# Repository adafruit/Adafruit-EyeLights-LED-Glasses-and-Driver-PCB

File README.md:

## Adafruit EyeLights LED Glasses and Driver PCB

<a href="http://www.adafruit.com/products/5217"><br/>
Click here to purchase the EyeLights Glasses Driver from the Adafruit shop</a>
<a href="http://www.adafruit.com/products/5210"><br/>
Click here to purchase the EyeLights Glasses from the Adafruit shop</a>

PCB files for the Adafruit EyeLights LED Glasses and Driver. 

Format is EagleCAD schematic and board layout
* https://www.adafruit.com/product/5217
* https://www.adafruit.com/product/5210

### Description

This board is designed to be a thin, bluetooth-enabled driver board for our Adafruit LED Glasses RGB LED matrix. That said, it's a perfectly good stand-alone development board for the Nordic nRF52840 chipset, with a very slim design, optional LiPo battery support, a few sensors, and a Stemma QT port for adding other devices or sensors with I2C plug-and-play.

The driver looks a little like a Feather but it does not have any breakout pins to keep it very compact. If you need access to GPIO pins, we recommend an nRF52840 ItsyBitsy, nRF52840 Feather or Feather Sense.

In exchange for GPIO outputs, we added some sensors on instead: each board comes with a LIS3DH triple-axis accelerometer that can be used for motion and orientation sensing, and a PDM digital microphone for audio sensing. To add more sensors or connect to the LED Glasses front panel, there's a  STEMMA QT connector for plug-and-play I2C support.

Unlike our Itsy/Feather boards, this driver also comes with a proper on/off switch which will cut power to the microcontroller and external sensors. There's optional LiPo charge support because we think that many folks will want to power this board with AAA or coin cell batteries. If you'd like to enable LiPo charging, short the jumper on the back and then make sure to only use 4.2V/3.7V rechargeable batteries in the battery port.

The nRF52840 is a lovely Bluetooth LE microcontroller, with good support in both Arduino and CircuitPython. It feathers a Cortex M4 processor with 1 MB of FLASH and 256KB of SRAM. Best of all, it's got that native USB! Finally, no need for a separate USB serial chip like CP2104 or FT232. Serial is handled as a USB CDC descriptor, and the chip can act like a keyboard, mouse, MIDI device or even disk drive. This chip has TinyUSB support - that means you can use it with Arduino as a native USB device and act as UART (CDC), HID, Mass Storage, MIDI and more!

Board Features:

* ARM Cortex M4F (with HW floating point acceleration) running at 64MHz
* 1MB flash and 256KB SRAM
* Bluetooth Low Energy compatible 2.4GHz radio (Details available in the nRF52840 product specification)
* FCC / IC / TELEC certified module with up to +8dBm output power
* 2MB external QSPI flash for CircuitPython file storage
* Built in LIS3DH accelerometer and PDM microphone
* Red LED for general purpose blinking, plus a tiny NeoPixel for colorful feedback
* STEMMA QT connector for plug-and-play I2C support.
* JST PH 2-pin battery port with optional LiPoly charger
* 4 mounting holes/slots
* Reset button and User button
* Native USB supported by every OS - can be used in Arduino or CircuitPython as USB serial console, Keyboard/Mouse HID, even a little disk drive for storing Python scripts.
* Can be used with Arduino IDE or CircuitPython
* Comes pre-loaded with the UF2 bootloader, which looks like a USB storage key. Simply drag firmware on to program, no special tools or drivers needed! It can be used to load up CircuitPython or Arduino IDE

For developers, we pre-programed the chip with our UF2 bootloader, which can use either command line UART programming with nrfutil (we use this for Arduino) or drag-n-drop mass storage, for CircuitPython installation and also because mass-storage-drive bootloaders make updating firmware so easy. Want to program the chip directly? You can use our command line tools with your favorite editor and toolchain. If you want to use an SWD programmer/debugger (for even more advanced usage), we have broken out the SWD pads for easy soldering.

Have you always wanted to upgrade your ensemble with a creepy-cool creature PCB silkscreen and an eye-blistering arrangement of LEDs? We love to put NeoPixels on our face, as evidenced by our many glowy LED glasses projects. Each of these requires quite a bit of soldering, and the cost of each NeoPixel adds up quickly. So we wanted to make a PCB assembly that can be used by any microcontroller to make glamorous face-tronics.

The Adafruit LED Glasses Front Panel has 116 artfully arranged 2x2mm RGB LEDs, all controlled with an IS31FL3741 I2C Driver that handles all the PWMing, so it's plug-and-play with almost any microcontroller.

On each side are STEMMA QT / JST-SH plugs - use these with one of our cables to attach it to your driver board of choice. Of course, you can pick left or right, then if you want to add on more hardware, like an accelerometer or light sensor, you can chain onto the other side. There's also six mounting holes for attaching to a glasses frame of your choosing - we recommend getting some 'fashion frames' from the mall or a street vendor, they're all the style and will provide a great mechanical support.

We have four different silkscreen designs: Bug, Wolf, Cat, and Dragon (peep those fearsome fangs!) Each design is exactly the same mechanically and electrically, the only difference is what is silkscreened on top of the PCB.

Gaze upon these features:

* IS31Fl3741 LED driver chip uses I2C to control the LEDs with 8-bit PWM per color (24-bit per RGB LED), write pixel data and it will handle the matrix driving automatically.
* Power and communicate over STEMMA QT for easy wiring
* The LEDs are arranged as 2 x 24-LED rings around each eye and an overlapping 16x5 matrix. The matrix has two bottom pixels 'missing' over the nose. Some LEDs are shared between both matrix and rings!
* Arduino and CircuitPython/Python library support

### License

Adafruit invests time and resources providing this open source design, please support Adafruit and open-source hardware by purchasing products from [Adafruit](https://www.adafruit.com)!

Designed by Limor Fried/Ladyada for Adafruit Industries.

Creative Commons Attribution/Share-Alike, all text above must be included in any redistribution. 
See license.txt for additional details.

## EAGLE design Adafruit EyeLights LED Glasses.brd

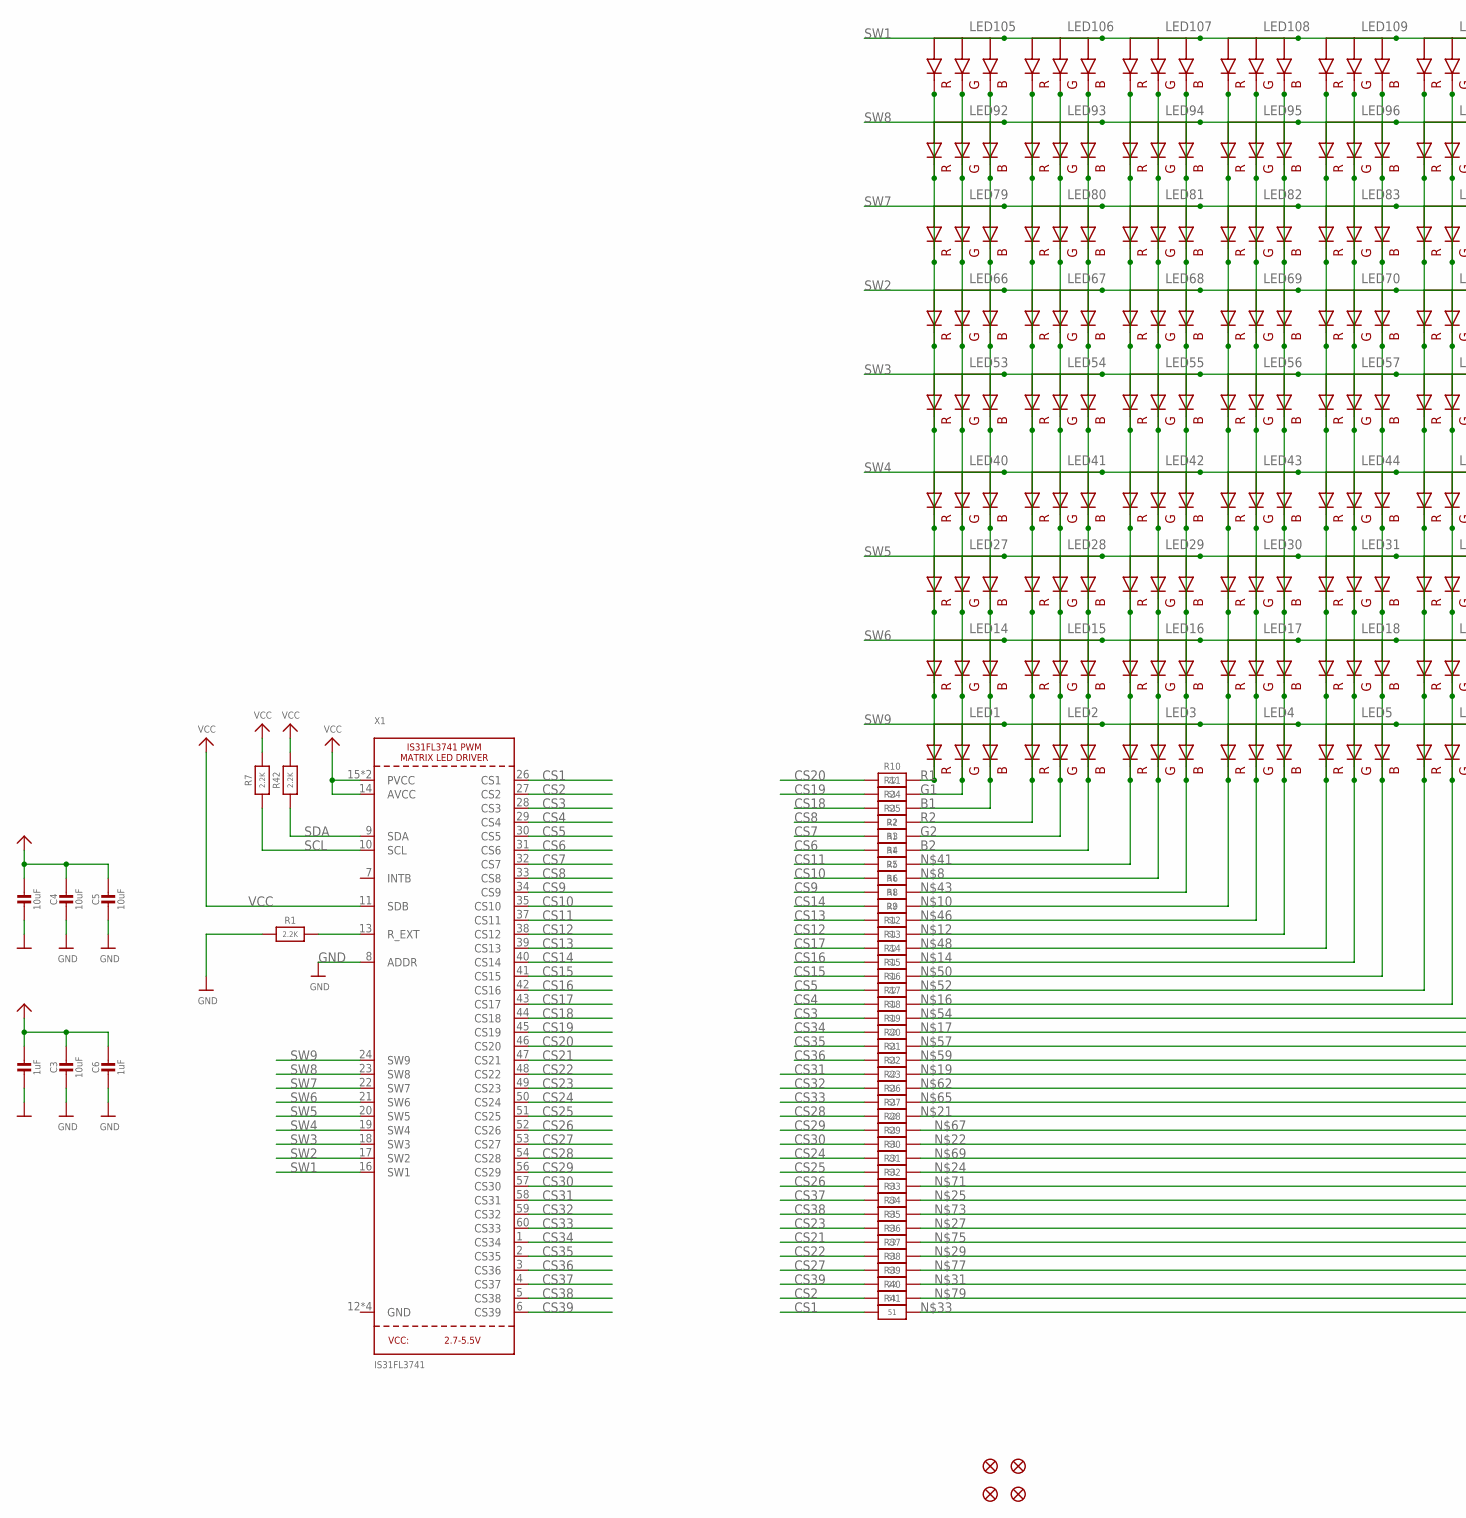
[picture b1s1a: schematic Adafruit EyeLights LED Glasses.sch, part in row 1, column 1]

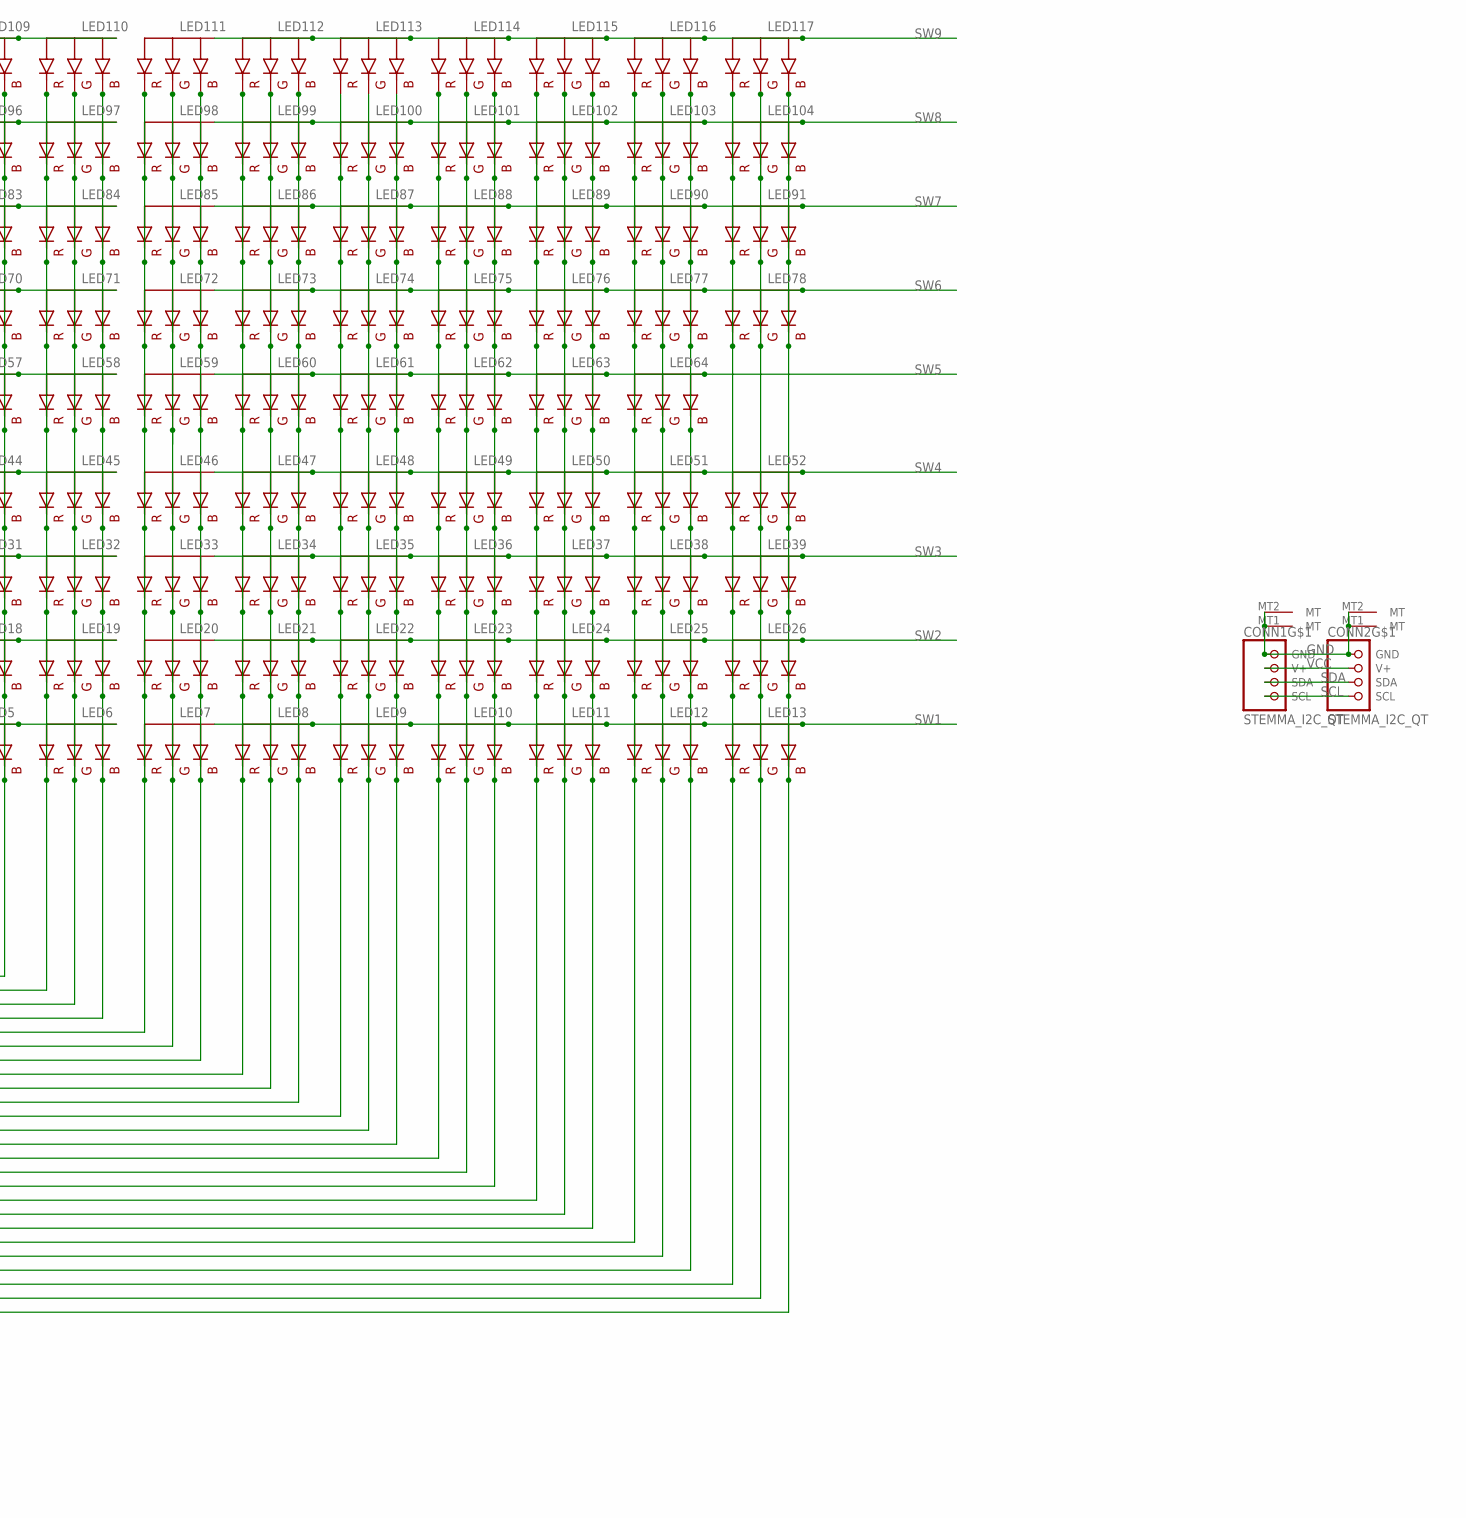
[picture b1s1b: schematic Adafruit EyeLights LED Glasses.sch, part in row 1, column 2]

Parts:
C1, C3, C4, C5: 10uF; 0805-NO
C2, C6: 1uF; 0603-NO
CONN1, CONN2: STEMMA_I2C_QT; JST_SH4
FID1, FID2, FID3, FID4: FIDUCIAL_1MM
LED1, LED2, LED3, LED4, LED5, LED6, LED7, LED8, LED9, LED10, LED11, LED12, LED13, LED14, LED15, LED16, LED17, LED18, LED19, LED20, LED21, LED22, LED23, LED24, LED25, LED26, LED27, LED28, LED29, LED30, LED31, LED32, LED33, LED34, LED35, LED36, LED37, LED38, LED39, LED40, LED41, LED42, LED43, LED44, LED45, LED46, LED47, LED48, LED49, LED50, LED51, LED52, LED53, LED54, LED55, LED56, LED57, LED58, LED59, LED60, LED61, LED62, LED63, LED64, LED66, LED67, LED68, LED69, LED70, LED71, LED72, LED73, LED74, LED75, LED76, LED77, LED78, LED79, LED80, LED81, LED82, LED83, LED84, LED85, LED86, LED87, LED88, LED89, LED90, LED91, LED92, LED93, LED94, LED95, LED96, LED97, LED98, LED99, LED100, LED101, LED102, LED103, LED104, LED105, LED106, LED107, LED108, LED109, LED110, LED111, LED112, LED113, LED114, LED115, LED116, LED117: RGBLED_CA_2121; RGBLED_2121
R1, R7, R42: 2.2K; 0603-NO
R2, R3, R5, R6, R9, R11, R12, R14, R15, R17, R18, R20, R21, R23, R24, R26, R28, R29, R31, R32, R34, R35, R37, R38, R40, R41: 51; 0603-NO
R4, R8, R10, R13, R16, R19, R22, R25, R27, R30, R33, R36, R39: 22; 0603-NO
X1: IS31FL3741; QFN60_7MM

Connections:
B1: LED1.B (BLUE), LED14.B (BLUE), LED27.B (BLUE), LED40.B (BLUE), LED53.B (BLUE), LED66.B (BLUE), LED79.B (BLUE), LED92.B (BLUE), LED105.B (BLUE), R24.2
B2: LED2.B (BLUE), LED15.B (BLUE), LED28.B (BLUE), LED41.B (BLUE), LED54.B (BLUE), LED67.B (BLUE), LED80.B (BLUE), LED93.B (BLUE), LED106.B (BLUE), R3.2
CS1: R41.1, X1.26 (CS1)
CS2: R40.1, X1.27 (CS2)
CS3: R18.1, X1.28 (CS3)
CS4: R17.1, X1.29 (CS4)
CS5: R16.1, X1.30 (CS5)
CS6: R3.1, X1.31 (CS6)
CS7: R2.1, X1.32 (CS7)
CS8: R25.1, X1.33 (CS8)
CS9: R6.1, X1.34 (CS9)
CS10: R5.1, X1.35 (CS10)
CS11: R4.1, X1.37 (CS11)
CS12: R12.1, X1.38 (CS12)
CS13: R9.1, X1.39 (CS13)
CS14: R8.1, X1.40 (CS14)
CS15: R15.1, X1.41 (CS15)
CS16: R14.1, X1.42 (CS16)
CS17: R13.1, X1.43 (CS17)
CS18: R24.1, X1.44 (CS18)
CS19: R11.1, X1.45 (CS19)
CS20: R10.1, X1.46 (CS20)
CS21: R36.1, X1.47 (CS21)
CS22: R37.1, X1.48 (CS22)
CS23: R35.1, X1.49 (CS23)
CS24: R30.1, X1.50 (CS24)
CS25: R31.1, X1.51 (CS25)
CS26: R32.1, X1.52 (CS26)
CS27: R38.1, X1.53 (CS27)
CS28: R27.1, X1.54 (CS28)
CS29: R28.1, X1.56 (CS29)
CS30: R29.1, X1.57 (CS30)
CS31: R22.1, X1.58 (CS31)
CS32: R23.1, X1.59 (CS32)
CS33: R26.1, X1.60 (CS33)
CS34: R19.1, X1.1 (CS34)
CS35: R20.1, X1.2 (CS35)
CS36: R21.1, X1.3 (CS36)
CS37: R33.1, X1.4 (CS37)
CS38: R34.1, X1.5 (CS38)
CS39: R39.1, X1.6 (CS39)
G1: LED1.G (GREEN), LED14.G (GREEN), LED27.G (GREEN), LED40.G (GREEN), LED53.G (GREEN), LED66.G (GREEN), LED79.G (GREEN), LED92.G (GREEN), LED105.G (GREEN), R11.2
G2: LED2.G (GREEN), LED15.G (GREEN), LED28.G (GREEN), LED41.G (GREEN), LED54.G (GREEN), LED67.G (GREEN), LED80.G (GREEN), LED93.G (GREEN), LED106.G (GREEN), R2.2
GND: C1.2, C2.2, C3.2, C4.2, C5.2, C6.2, CONN1.1 (GND), CONN1.MT1 (MT), CONN1.MT2 (MT), CONN2.1 (GND), CONN2.MT1 (MT), CONN2.MT2 (MT), R1.1, X1.8 (ADDR), X1.12 (GND), X1.36 (GND), X1.55 (GND), X1.THERMAL (GND)
unnamed: R1.2, X1.13 (R_EXT)
unnamed: LED3.G (GREEN), LED16.G (GREEN), LED29.G (GREEN), LED42.G (GREEN), LED55.G (GREEN), LED68.G (GREEN), LED81.G (GREEN), LED94.G (GREEN), LED107.G (GREEN), R5.2
unnamed: LED4.R (RED), LED17.R (RED), LED30.R (RED), LED43.R (RED), LED56.R (RED), LED69.R (RED), LED82.R (RED), LED95.R (RED), LED108.R (RED), R8.2
unnamed: LED4.B (BLUE), LED17.B (BLUE), LED30.B (BLUE), LED43.B (BLUE), LED56.B (BLUE), LED69.B (BLUE), LED82.B (BLUE), LED95.B (BLUE), LED108.B (BLUE), R12.2
unnamed: LED5.G (GREEN), LED18.G (GREEN), LED31.G (GREEN), LED44.G (GREEN), LED57.G (GREEN), LED70.G (GREEN), LED83.G (GREEN), LED96.G (GREEN), LED109.G (GREEN), R14.2
unnamed: LED6.G (GREEN), LED19.G (GREEN), LED32.G (GREEN), LED45.G (GREEN), LED58.G (GREEN), LED71.G (GREEN), LED84.G (GREEN), LED97.G (GREEN), LED110.G (GREEN), R17.2
unnamed: LED7.R (RED), LED20.R (RED), LED33.R (RED), LED46.R (RED), LED59.R (RED), LED72.R (RED), LED85.R (RED), LED98.R (RED), LED111.R (RED), R19.2
unnamed: LED8.R (RED), LED21.R (RED), LED34.R (RED), LED47.R (RED), LED60.R (RED), LED73.R (RED), LED86.R (RED), LED99.R (RED), LED112.R (RED), R22.2
unnamed: LED9.R (RED), LED22.R (RED), LED35.R (RED), LED48.R (RED), LED61.R (RED), LED74.R (RED), LED87.R (RED), LED100.R (RED), LED113.R (RED), R27.2
unnamed: LED9.B (BLUE), LED22.B (BLUE), LED35.B (BLUE), LED48.B (BLUE), LED61.B (BLUE), LED74.B (BLUE), LED87.B (BLUE), LED100.B (BLUE), LED113.B (BLUE), R29.2
unnamed: LED10.G (GREEN), LED23.G (GREEN), LED36.G (GREEN), LED49.G (GREEN), LED62.G (GREEN), LED75.G (GREEN), LED88.G (GREEN), LED101.G (GREEN), LED114.G (GREEN), R31.2
unnamed: LED11.R (RED), LED24.R (RED), LED37.R (RED), LED50.R (RED), LED63.R (RED), LED76.R (RED), LED89.R (RED), LED102.R (RED), LED115.R (RED), R33.2
unnamed: LED11.B (BLUE), LED24.B (BLUE), LED37.B (BLUE), LED50.B (BLUE), LED63.B (BLUE), LED76.B (BLUE), LED89.B (BLUE), LED102.B (BLUE), LED115.B (BLUE), R35.2
unnamed: LED12.G (GREEN), LED25.G (GREEN), LED38.G (GREEN), LED51.G (GREEN), LED64.G (GREEN), LED77.G (GREEN), LED90.G (GREEN), LED103.G (GREEN), LED116.G (GREEN), R37.2
unnamed: LED13.R (RED), LED26.R (RED), LED39.R (RED), LED52.R (RED), LED78.R (RED), LED91.R (RED), LED104.R (RED), LED117.R (RED), R39.2
unnamed: LED13.B (BLUE), LED26.B (BLUE), LED39.B (BLUE), LED52.B (BLUE), LED78.B (BLUE), LED91.B (BLUE), LED104.B (BLUE), LED117.B (BLUE), R41.2
unnamed: LED3.R (RED), LED16.R (RED), LED29.R (RED), LED42.R (RED), LED55.R (RED), LED68.R (RED), LED81.R (RED), LED94.R (RED), LED107.R (RED), R4.2
unnamed: LED3.B (BLUE), LED16.B (BLUE), LED29.B (BLUE), LED42.B (BLUE), LED55.B (BLUE), LED68.B (BLUE), LED81.B (BLUE), LED94.B (BLUE), LED107.B (BLUE), R6.2
unnamed: LED4.G (GREEN), LED17.G (GREEN), LED30.G (GREEN), LED43.G (GREEN), LED56.G (GREEN), LED69.G (GREEN), LED82.G (GREEN), LED95.G (GREEN), LED108.G (GREEN), R9.2
unnamed: LED5.R (RED), LED18.R (RED), LED31.R (RED), LED44.R (RED), LED57.R (RED), LED70.R (RED), LED83.R (RED), LED96.R (RED), LED109.R (RED), R13.2
unnamed: LED5.B (BLUE), LED18.B (BLUE), LED31.B (BLUE), LED44.B (BLUE), LED57.B (BLUE), LED70.B (BLUE), LED83.B (BLUE), LED96.B (BLUE), LED109.B (BLUE), R15.2
unnamed: LED6.R (RED), LED19.R (RED), LED32.R (RED), LED45.R (RED), LED58.R (RED), LED71.R (RED), LED84.R (RED), LED97.R (RED), LED110.R (RED), R16.2
unnamed: LED6.B (BLUE), LED19.B (BLUE), LED32.B (BLUE), LED45.B (BLUE), LED58.B (BLUE), LED71.B (BLUE), LED84.B (BLUE), LED97.B (BLUE), LED110.B (BLUE), R18.2
unnamed: LED7.G (GREEN), LED20.G (GREEN), LED33.G (GREEN), LED46.G (GREEN), LED59.G (GREEN), LED72.G (GREEN), LED85.G (GREEN), LED98.G (GREEN), LED111.G (GREEN), R20.2
unnamed: LED7.B (BLUE), LED20.B (BLUE), LED33.B (BLUE), LED46.B (BLUE), LED59.B (BLUE), LED72.B (BLUE), LED85.B (BLUE), LED98.B (BLUE), LED111.B (BLUE), R21.2
unnamed: LED8.G (GREEN), LED21.G (GREEN), LED34.G (GREEN), LED47.G (GREEN), LED60.G (GREEN), LED73.G (GREEN), LED86.G (GREEN), LED99.G (GREEN), LED112.G (GREEN), R23.2
unnamed: LED8.B (BLUE), LED21.B (BLUE), LED34.B (BLUE), LED47.B (BLUE), LED60.B (BLUE), LED73.B (BLUE), LED86.B (BLUE), LED99.B (BLUE), LED112.B (BLUE), R26.2
unnamed: LED9.G (GREEN), LED22.G (GREEN), LED35.G (GREEN), LED48.G (GREEN), LED61.G (GREEN), LED74.G (GREEN), LED87.G (GREEN), LED100.G (GREEN), LED113.G (GREEN), R28.2
unnamed: LED10.R (RED), LED23.R (RED), LED36.R (RED), LED49.R (RED), LED62.R (RED), LED75.R (RED), LED88.R (RED), LED101.R (RED), LED114.R (RED), R30.2
unnamed: LED10.B (BLUE), LED23.B (BLUE), LED36.B (BLUE), LED49.B (BLUE), LED62.B (BLUE), LED75.B (BLUE), LED88.B (BLUE), LED101.B (BLUE), LED114.B (BLUE), R32.2
unnamed: LED11.G (GREEN), LED24.G (GREEN), LED37.G (GREEN), LED50.G (GREEN), LED63.G (GREEN), LED76.G (GREEN), LED89.G (GREEN), LED102.G (GREEN), LED115.G (GREEN), R34.2
unnamed: LED12.R (RED), LED25.R (RED), LED38.R (RED), LED51.R (RED), LED64.R (RED), LED77.R (RED), LED90.R (RED), LED103.R (RED), LED116.R (RED), R36.2
unnamed: LED12.B (BLUE), LED25.B (BLUE), LED38.B (BLUE), LED51.B (BLUE), LED64.B (BLUE), LED77.B (BLUE), LED90.B (BLUE), LED103.B (BLUE), LED116.B (BLUE), R38.2
unnamed: LED13.G (GREEN), LED26.G (GREEN), LED39.G (GREEN), LED52.G (GREEN), LED78.G (GREEN), LED91.G (GREEN), LED104.G (GREEN), LED117.G (GREEN), R40.2
R1: LED1.R (RED), LED14.R (RED), LED27.R (RED), LED40.R (RED), LED53.R (RED), LED66.R (RED), LED79.R (RED), LED92.R (RED), LED105.R (RED), R10.2
R2: LED2.R (RED), LED15.R (RED), LED28.R (RED), LED41.R (RED), LED54.R (RED), LED67.R (RED), LED80.R (RED), LED93.R (RED), LED106.R (RED), R25.2
SCL: CONN1.4 (SCL), CONN2.4 (SCL), R7.1, X1.10 (SCL)
SDA: CONN1.3 (SDA), CONN2.3 (SDA), R42.1, X1.9 (SDA)
SW1: LED7.A (VCC), LED8.A (VCC), LED9.A (VCC), LED10.A (VCC), LED11.A (VCC), LED12.A (VCC), LED13.A (VCC), LED105.A (VCC), LED106.A (VCC), LED107.A (VCC), LED108.A (VCC), LED109.A (VCC), LED110.A (VCC), X1.16 (SW1)
SW2: LED20.A (VCC), LED21.A (VCC), LED22.A (VCC), LED23.A (VCC), LED24.A (VCC), LED25.A (VCC), LED26.A (VCC), LED66.A (VCC), LED67.A (VCC), LED68.A (VCC), LED69.A (VCC), LED70.A (VCC), LED71.A (VCC), X1.17 (SW2)
SW3: LED33.A (VCC), LED34.A (VCC), LED35.A (VCC), LED36.A (VCC), LED37.A (VCC), LED38.A (VCC), LED39.A (VCC), LED53.A (VCC), LED54.A (VCC), LED55.A (VCC), LED56.A (VCC), LED57.A (VCC), LED58.A (VCC), X1.18 (SW3)
SW4: LED40.A (VCC), LED41.A (VCC), LED42.A (VCC), LED43.A (VCC), LED44.A (VCC), LED45.A (VCC), LED46.A (VCC), LED47.A (VCC), LED48.A (VCC), LED49.A (VCC), LED50.A (VCC), LED51.A (VCC), LED52.A (VCC), X1.19 (SW4)
SW5: LED27.A (VCC), LED28.A (VCC), LED29.A (VCC), LED30.A (VCC), LED31.A (VCC), LED32.A (VCC), LED59.A (VCC), LED60.A (VCC), LED61.A (VCC), LED62.A (VCC), LED63.A (VCC), LED64.A (VCC), X1.20 (SW5)
SW6: LED14.A (VCC), LED15.A (VCC), LED16.A (VCC), LED17.A (VCC), LED18.A (VCC), LED19.A (VCC), LED72.A (VCC), LED73.A (VCC), LED74.A (VCC), LED75.A (VCC), LED76.A (VCC), LED77.A (VCC), LED78.A (VCC), X1.21 (SW6)
SW7: LED79.A (VCC), LED80.A (VCC), LED81.A (VCC), LED82.A (VCC), LED83.A (VCC), LED84.A (VCC), LED85.A (VCC), LED86.A (VCC), LED87.A (VCC), LED88.A (VCC), LED89.A (VCC), LED90.A (VCC), LED91.A (VCC), X1.22 (SW7)
SW8: LED92.A (VCC), LED93.A (VCC), LED94.A (VCC), LED95.A (VCC), LED96.A (VCC), LED97.A (VCC), LED98.A (VCC), LED99.A (VCC), LED100.A (VCC), LED101.A (VCC), LED102.A (VCC), LED103.A (VCC), LED104.A (VCC), X1.23 (SW8)
SW9: LED1.A (VCC), LED2.A (VCC), LED3.A (VCC), LED4.A (VCC), LED5.A (VCC), LED6.A (VCC), LED111.A (VCC), LED112.A (VCC), LED113.A (VCC), LED114.A (VCC), LED115.A (VCC), LED116.A (VCC), LED117.A (VCC), X1.24 (SW9)
VCC: C1.1, C2.1, C3.1, C4.1, C5.1, C6.1, CONN1.2 (V+), CONN2.2 (V+), R7.2, R42.2, X1.11 (SDB), X1.14 (AVCC), X1.15 (PVCC), X1.25 (PVCC)

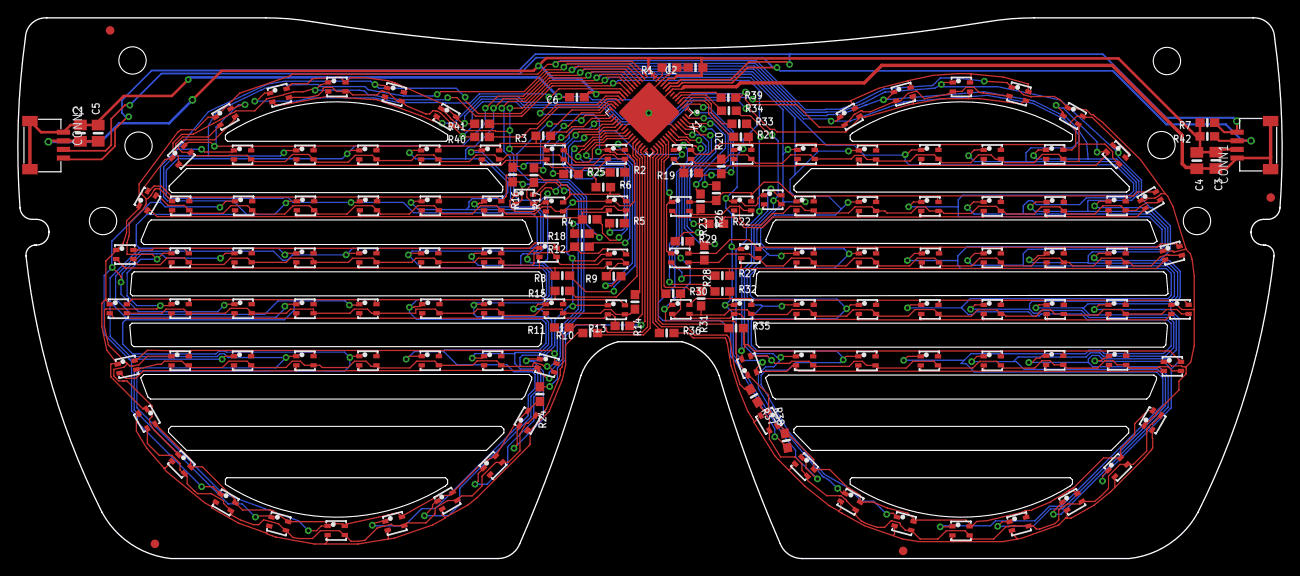
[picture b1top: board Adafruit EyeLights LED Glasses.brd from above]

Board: 2 copper layers, 147.0 x 62.9 mm, 171 parts (0 on the bottom side), 92 nets.

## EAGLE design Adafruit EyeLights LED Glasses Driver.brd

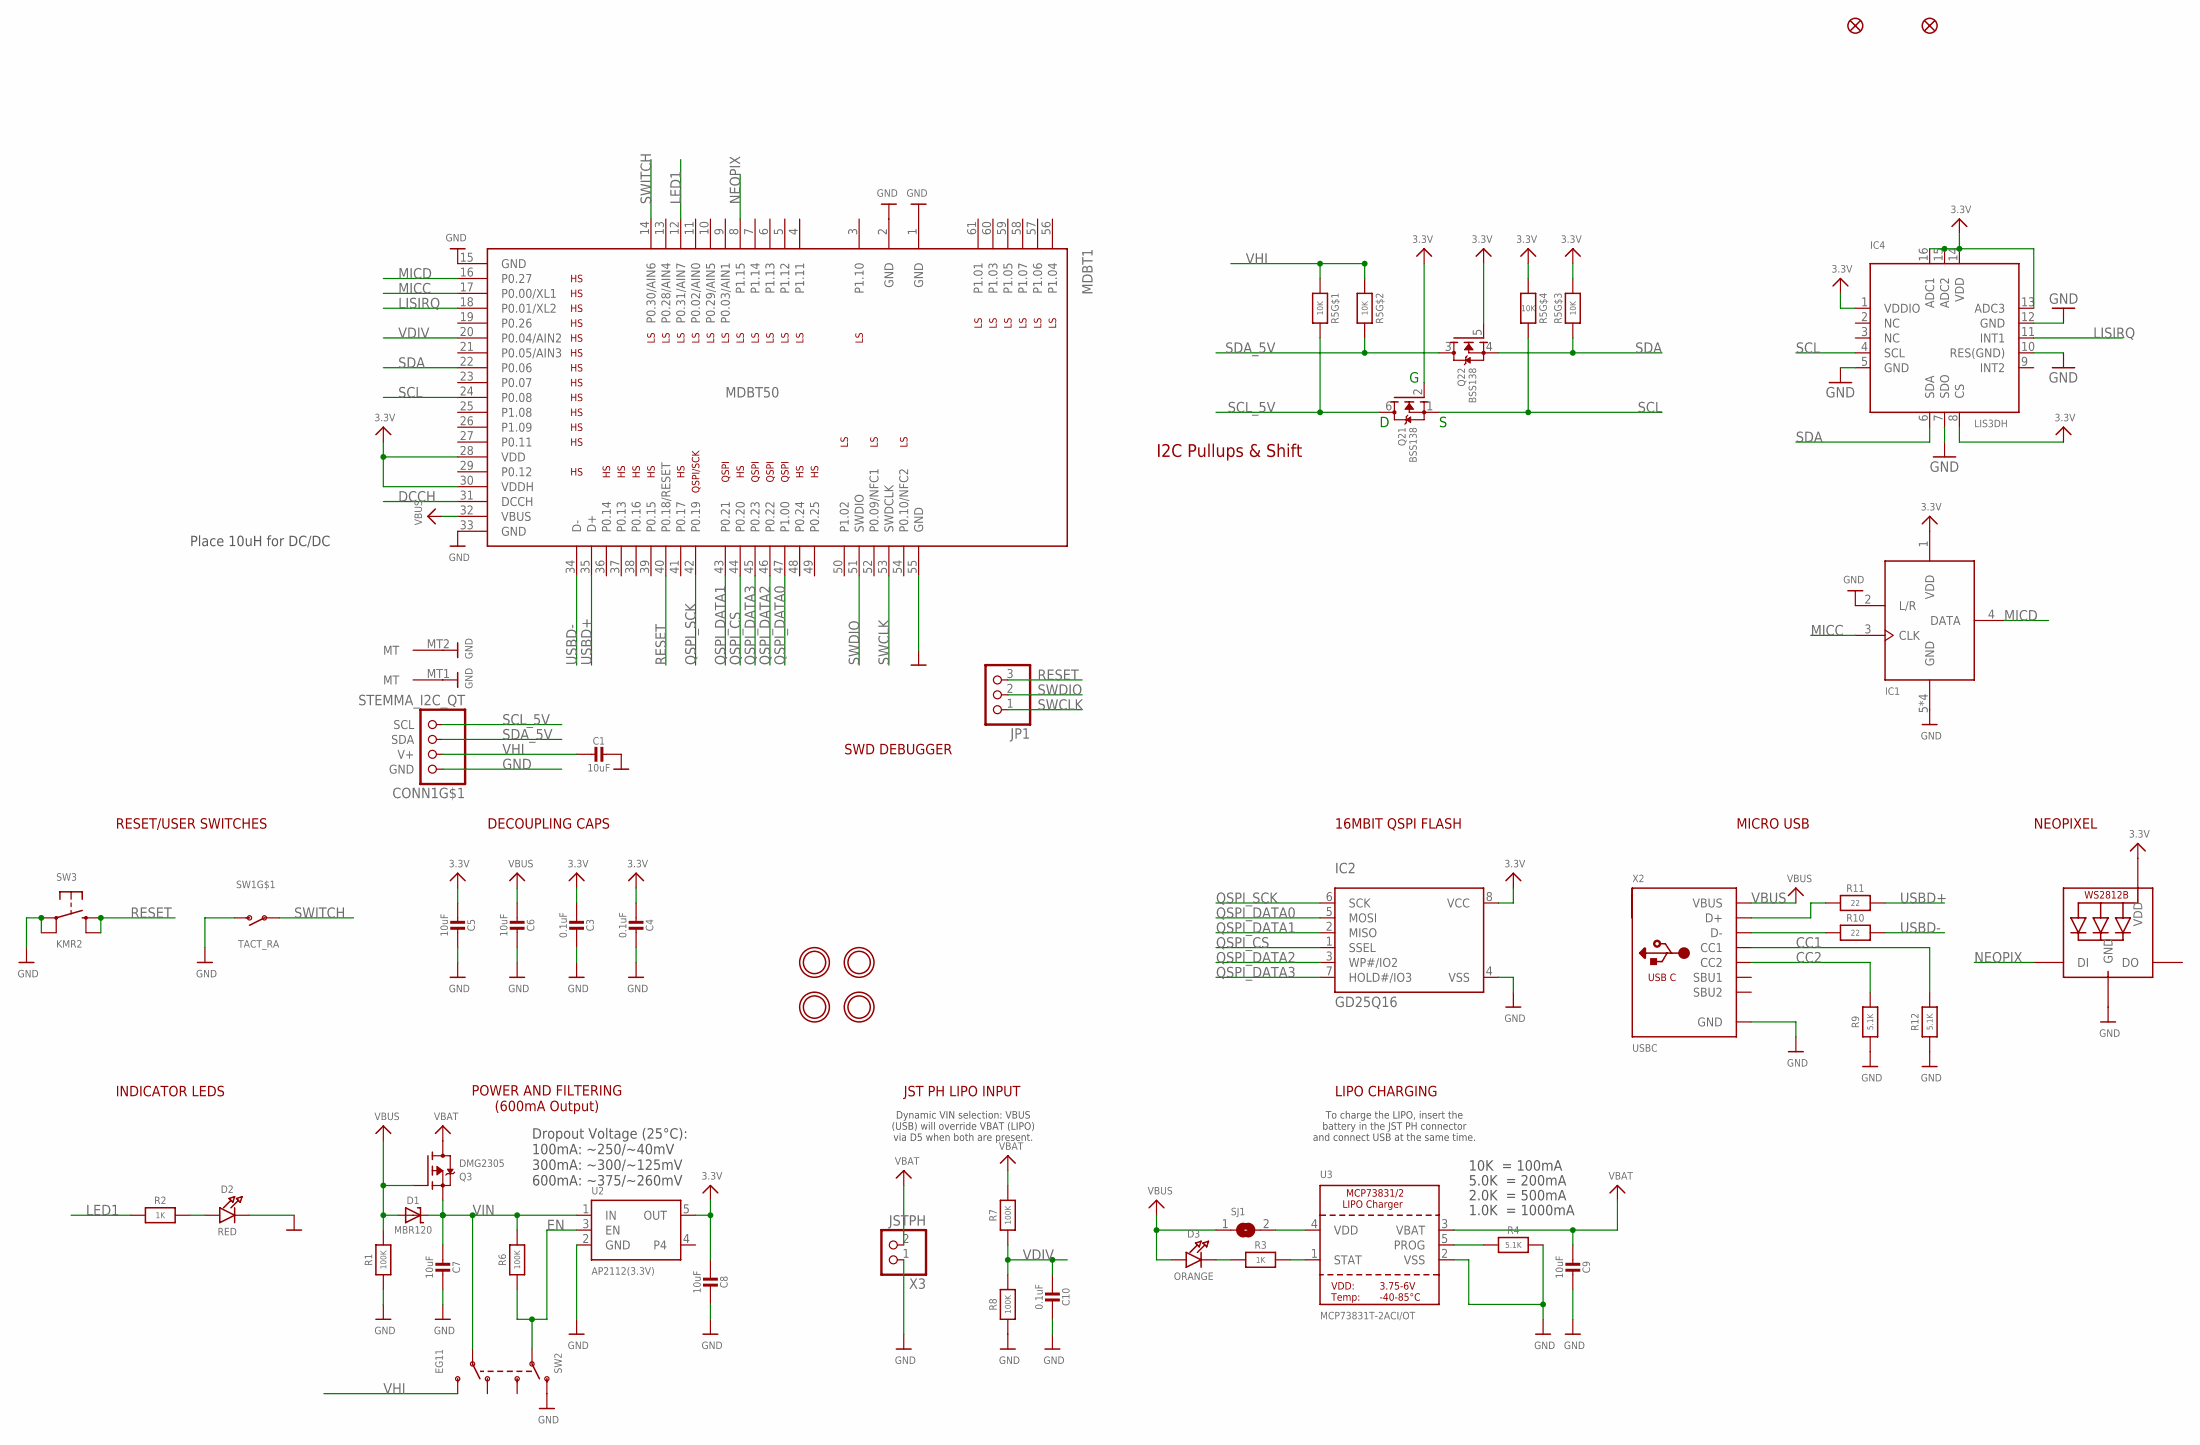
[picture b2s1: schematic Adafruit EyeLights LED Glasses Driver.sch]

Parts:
C1, C5, C6, C7, C8, C9: 10uF; 0805-NO
C3, C4, C10: 0.1uF; 0603-NO
CONN1: STEMMA_I2C_QT; JST_SH4
D1: MBR120; SOD-123
D2: RED; CHIPLED_0805_NOOUTLINE
D3: ORANGE; CHIPLED_0805_NOOUTLINE
FID1, FID2: FIDUCIAL_1MM
IC1: MIC_PDM_SPK0415; SPK0415HM4H
IC2: GD25Q16; SOIC8_150MIL
IC4: LIS3DH; LGA16_3X3MM
JP1: HEADER-1X3ROUND; 1X03_ROUND
LED1: WS2812B_SK6805_1515; SK6805_1515
MDBT1: MDBT50
Q2: BSS138; SOT363
Q3: DMG2305; SOT23-R
R1, R6, R7, R8: 100K; 0603-NO
R2, R3: 1K; 0603-NO
R4, R9, R12: 5.1K; 0603-NO
R5: 10K; RESPACK_4X0603
R10, R11: 22; 0603-NO
SJ1: SOLDERJUMPER; SOLDERJUMPER_ARROW_NOPASTE
SW1: TACT_RA; SPST_TACTILE_RA
SW2: EG11; EG1390
SW3: KMR2; BTN_KMR2_4.6X2.8
U2: AP2112(3.3V); SOT23-5
U3: MCP73831T-2ACI/OT; SOT23-5
U$10, U$12, U$14, U$16: MOUNTINGHOLE_SLOT4MM; SLOT_4MM_PLATED
X2: USBC; USB_C_CUSB31-CFM2AX-01-X
X3: JSTPH; JSTPH2_BATT

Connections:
3.3V: C3.2, C4.2, C5.2, C8.2, IC1.1 (VDD), IC2.8 (VCC), IC4.1 (VDDIO), IC4.8 (CS), IC4.13 (ADC3), IC4.14 (VDD), IC4.15 (ADC2), IC4.16 (ADC1), LED1.2 (VDD), MDBT1.28 (VDD), MDBT1.30 (VDDH), Q2.2 (G), Q2.5 (G), R5.3 (1), R5.5 (2), U2.5 (OUT)
CC1: R12.2, X2.A5 (CC1)
CC2: R9.2, X2.B5 (CC2)
D+: R11.1, X2.A6 (D+), X2.B6 (D+)
D-: R10.1, X2.A7 (D-), X2.B7 (D-)
DCCH: MDBT1.31 (DCCH)
EN: R6.1, SW2.P1, U2.3 (EN)
GND: C1.1, C3.1, C4.1, C5.1, C6.1, C7.1, C8.1, C9.1, C10.1, CONN1.1 (GND), CONN1.MT1 (MT), CONN1.MT2 (MT), D2.C, IC1.2 (L/R), IC1.5 (GND), IC1.6 (GND), IC1.7 (GND), IC1.8 (GND), IC2.4 (VSS), IC4.5 (GND), IC4.7 (SDO), IC4.10 (RES(GND)), IC4.12 (GND), LED1.4 (GND), MDBT1.1 (GND), MDBT1.2 (GND), MDBT1.15 (GND), MDBT1.33 (GND), MDBT1.55 (GND), R1.1, R4.2, R8.1, R9.1, R12.1, SW1.2 (S), SW2.O1, SW3.A, SW3.A' (P1), U2.2 (GND), U3.2 (VSS), X2.A1B12 (GND), X2.B1A12 (GND), X3.1
LED1: MDBT1.12 (P0.31/AIN7), R2.1
LISIRQ: IC4.11 (INT1), MDBT1.18 (P0.01/XL2)
MICC: IC1.3 (CLK), MDBT1.17 (P0.00/XL1)
MICD: IC1.4 (DATA), MDBT1.16 (P0.27)
unnamed: D3.C, R3.1
unnamed: SJ1.2, U3.4 (VDD)
unnamed: D2.A, R2.2
unnamed: R3.2, U3.1 (STAT)
unnamed: R4.1, U3.5 (PROG)
NEOPIX: LED1.1 (DI), MDBT1.8 (P1.15)
QSPI_CS: IC2.1 (SSEL), MDBT1.44 (P0.20)
QSPI_DATA0: IC2.5 (MOSI), MDBT1.47 (P1.00)
QSPI_DATA1: IC2.2 (MISO), MDBT1.43 (P0.21)
QSPI_DATA2: IC2.3 (WP#/IO2), MDBT1.46 (P0.22)
QSPI_DATA3: IC2.7 (HOLD#/IO3), MDBT1.45 (P0.23)
QSPI_SCK: IC2.6 (SCK), MDBT1.42 (P0.19)
RESET: JP1.3, MDBT1.40 (P0.18/RESET), SW3.B (S), SW3.B' (S1)
SCL: IC4.4 (SCL), MDBT1.24 (P0.08), Q2.1 (S), R5.4 (1)
SCL_5V: CONN1.4 (SCL), Q2.6 (D), R5.8 (2)
SDA: IC4.6 (SDA), MDBT1.22 (P0.06), Q2.4 (S), R5.6 (2)
SDA_5V: CONN1.3 (SDA), Q2.3 (D), R5.7 (2)
SWCLK: JP1.1, MDBT1.53 (SWDCLK)
SWDIO: JP1.2, MDBT1.51 (SWDIO)
SWITCH: MDBT1.14 (P0.30/AIN6), SW1.1
USBD+: MDBT1.35 (D+), R11.2
USBD-: MDBT1.34 (D-), R10.2
VBAT: C9.2, Q3.3 (D), R7.2, U3.3 (VBAT), X3.2
VBUS: C6.2, D1.A, D3.A, MDBT1.32 (VBUS), Q3.1 (G), R1.2, SJ1.1, X2.A4B9 (VBUS), X2.B4A9 (VBUS)
VDIV: C10.2, MDBT1.20 (P0.04/AIN2), R7.1, R8.2
VHI: C1.2, CONN1.2 (V+), R5.1, R5.2 (1), SW2.S2
VIN: C7.2, D1.C, Q3.2 (S), R6.2, SW2.P2, U2.1 (IN)

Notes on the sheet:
10K = 100mA
5.0K = 200mA
2.0K = 500mA
1.0K = 1000mA
LIPO CHARGING
To charge the LIPO, insert the battery in the JST PH connector and connect USB at the same time.
POWER AND FILTERING (600mA Output)
JST PH LIPO INPUT
Dynamic VIN selection: VBUS (USB) will override VBAT (LIPO) via D5 when both are present.
Dropout Voltage (25°C): 100mA: ~250/~40mV 300mA: ~300/~125mV 600mA: ~375/~260mV
INDICATOR LEDS
RESET/USER SWITCHES
DECOUPLING CAPS
SWD DEBUGGER
16MBIT QSPI FLASH
MICRO USB
NEOPIXEL
Place 10uH for DC/DC
I2C Pullups & Shift

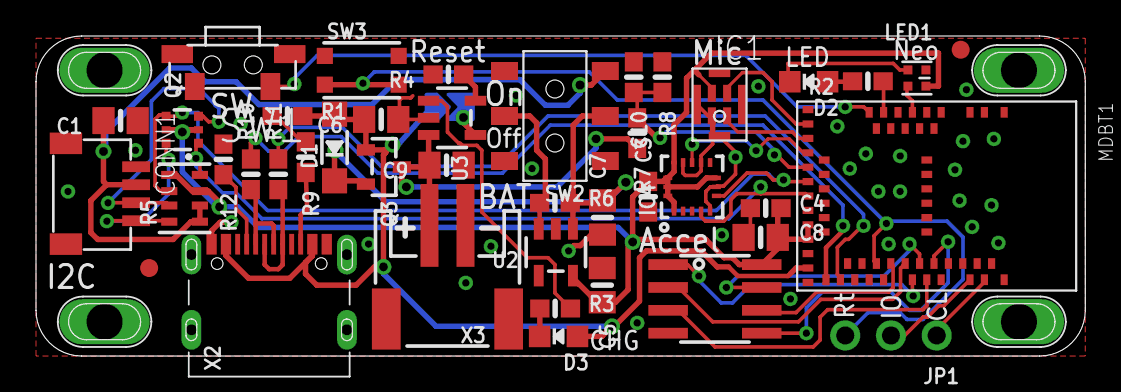
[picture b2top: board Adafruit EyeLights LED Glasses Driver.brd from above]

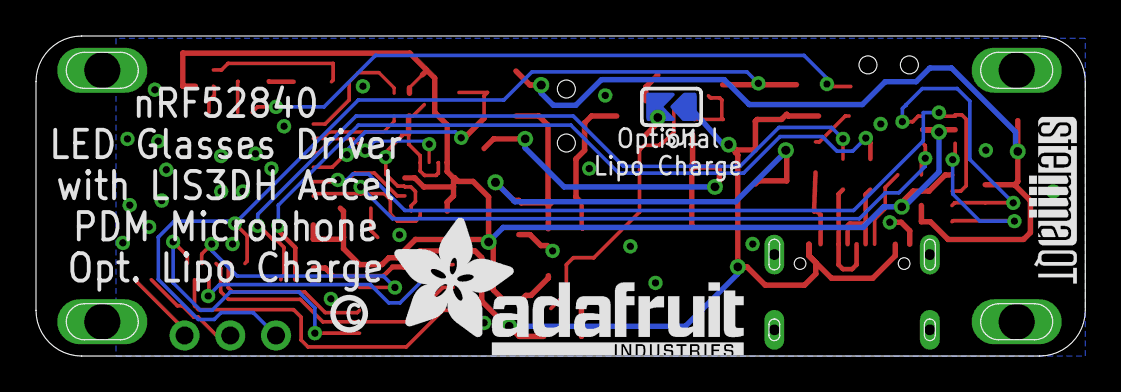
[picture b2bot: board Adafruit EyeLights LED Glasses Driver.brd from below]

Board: 2 copper layers, 58.3 x 17.8 mm, 50 parts (4 on the bottom side), 38 nets.

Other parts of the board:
U$28: STEMMAQT
U$37: ADAFRUIT_TEXT_20MM
U$63: PCBFEAT-REV-040

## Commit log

2021-10-05 Adding board files.
2021-10-07 Add pinout diagram.

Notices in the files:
parts and their libraries:
microbuilder: This work is placed in the public domain, and may be freely used for commercial and non-commercial work with the following conditions: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
